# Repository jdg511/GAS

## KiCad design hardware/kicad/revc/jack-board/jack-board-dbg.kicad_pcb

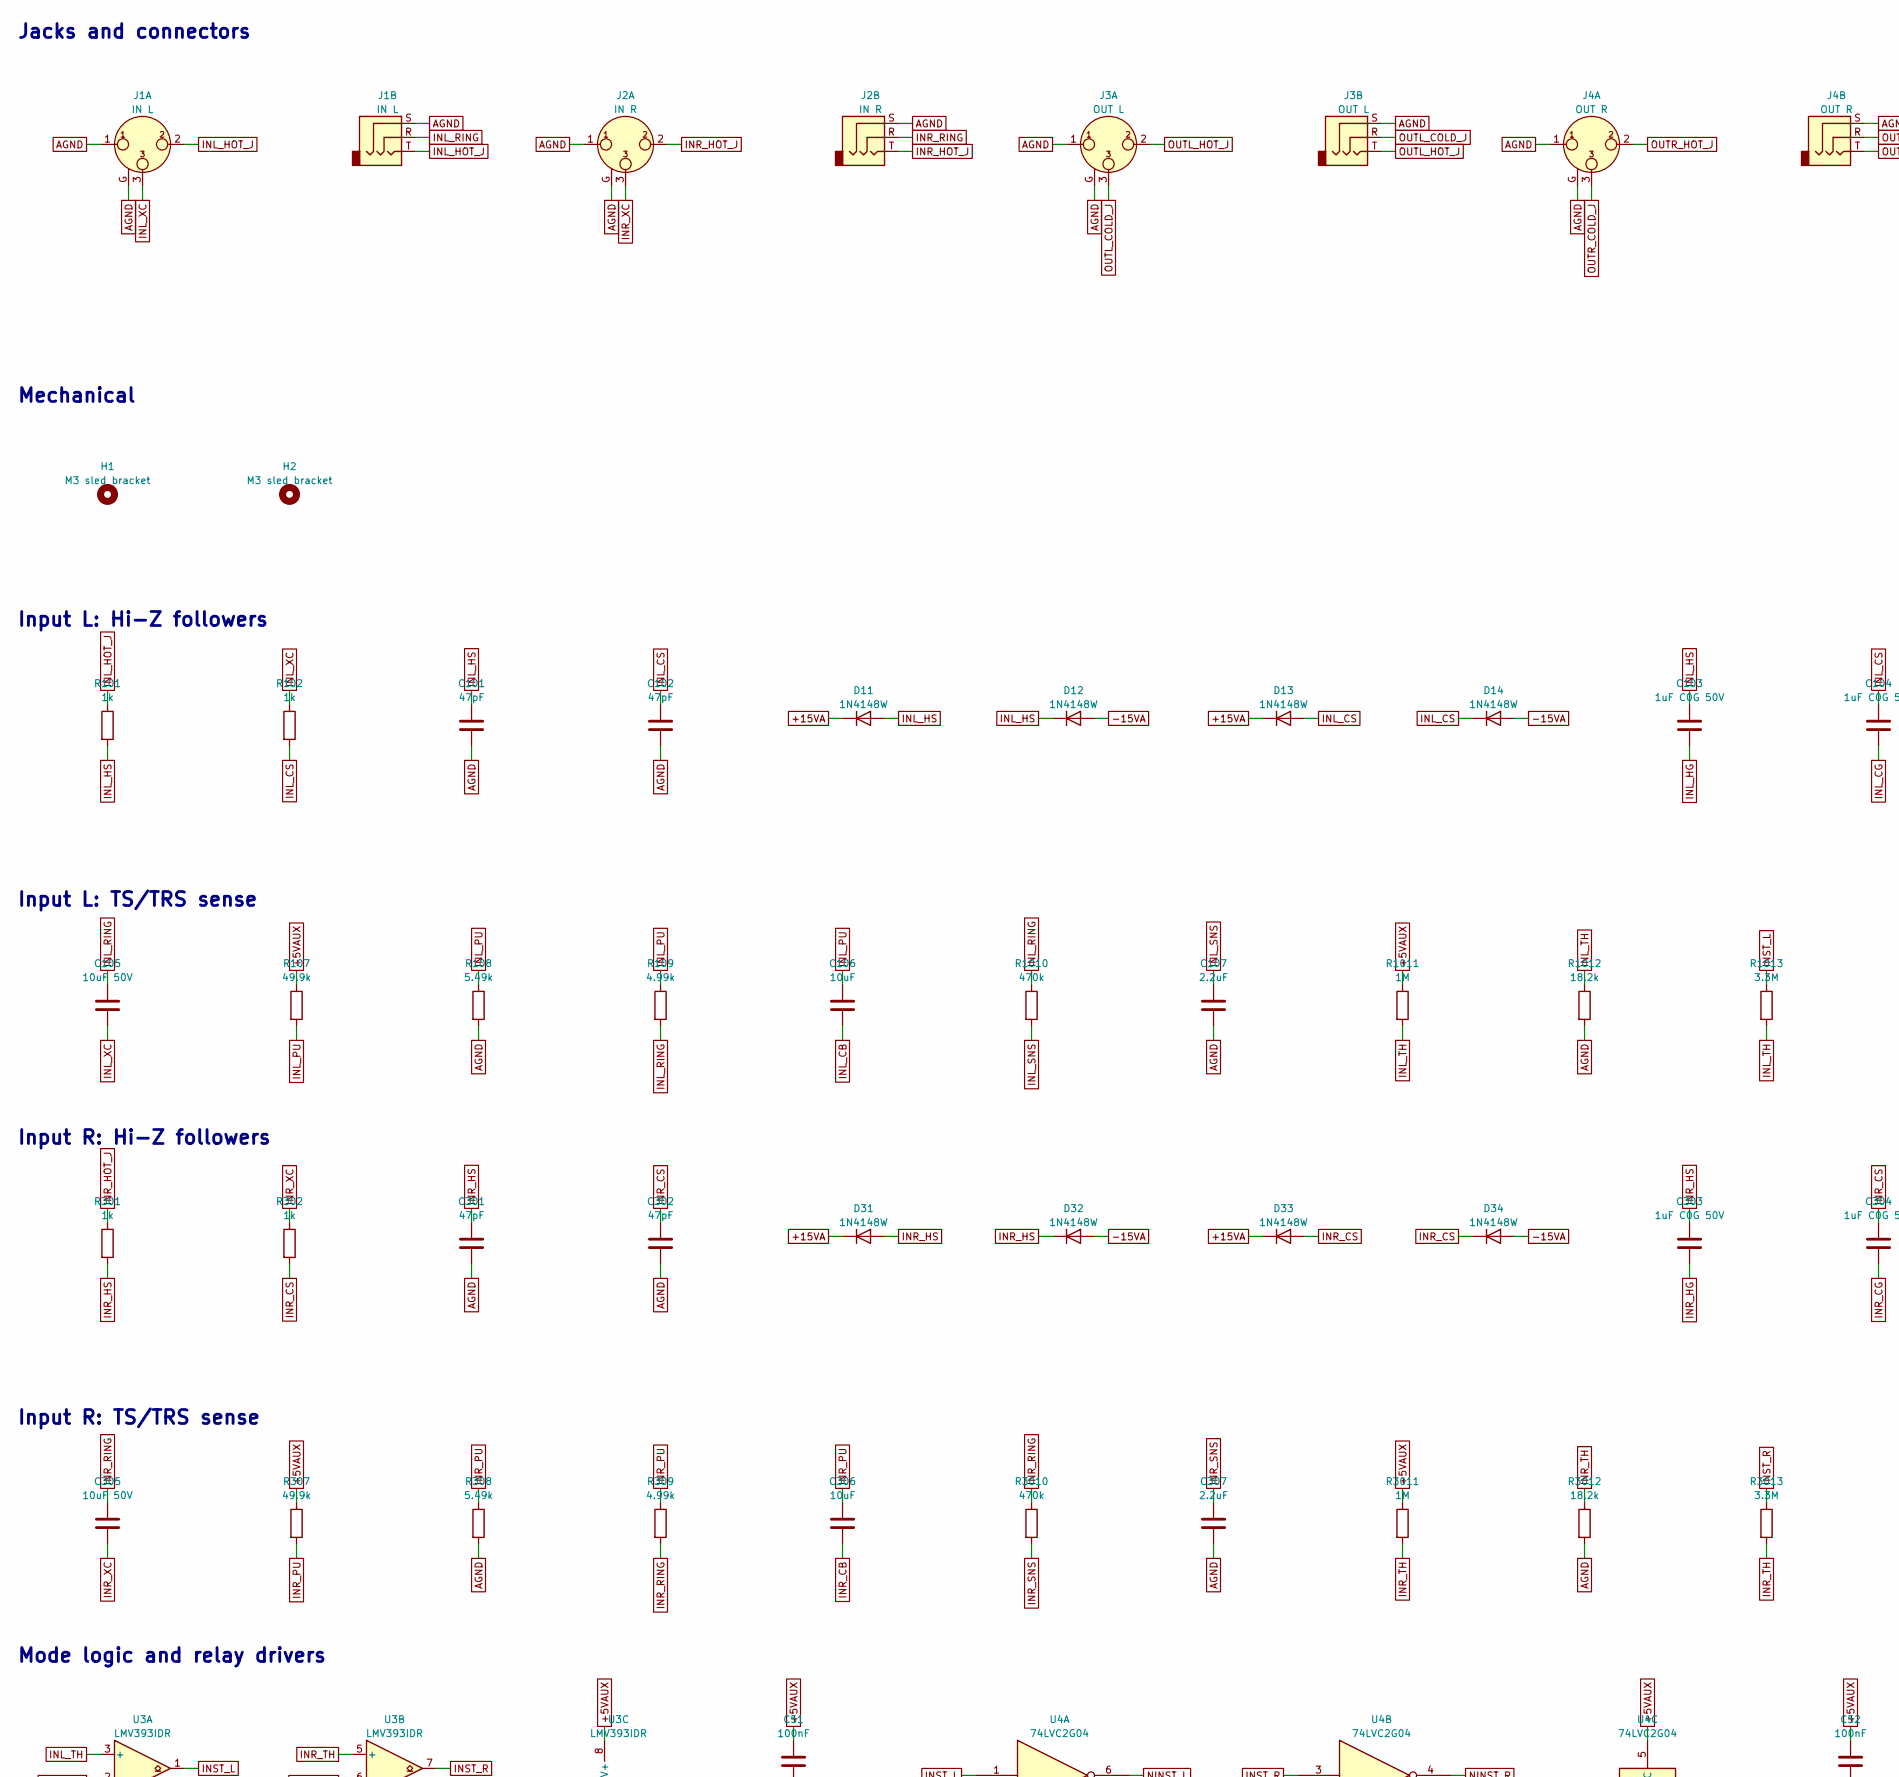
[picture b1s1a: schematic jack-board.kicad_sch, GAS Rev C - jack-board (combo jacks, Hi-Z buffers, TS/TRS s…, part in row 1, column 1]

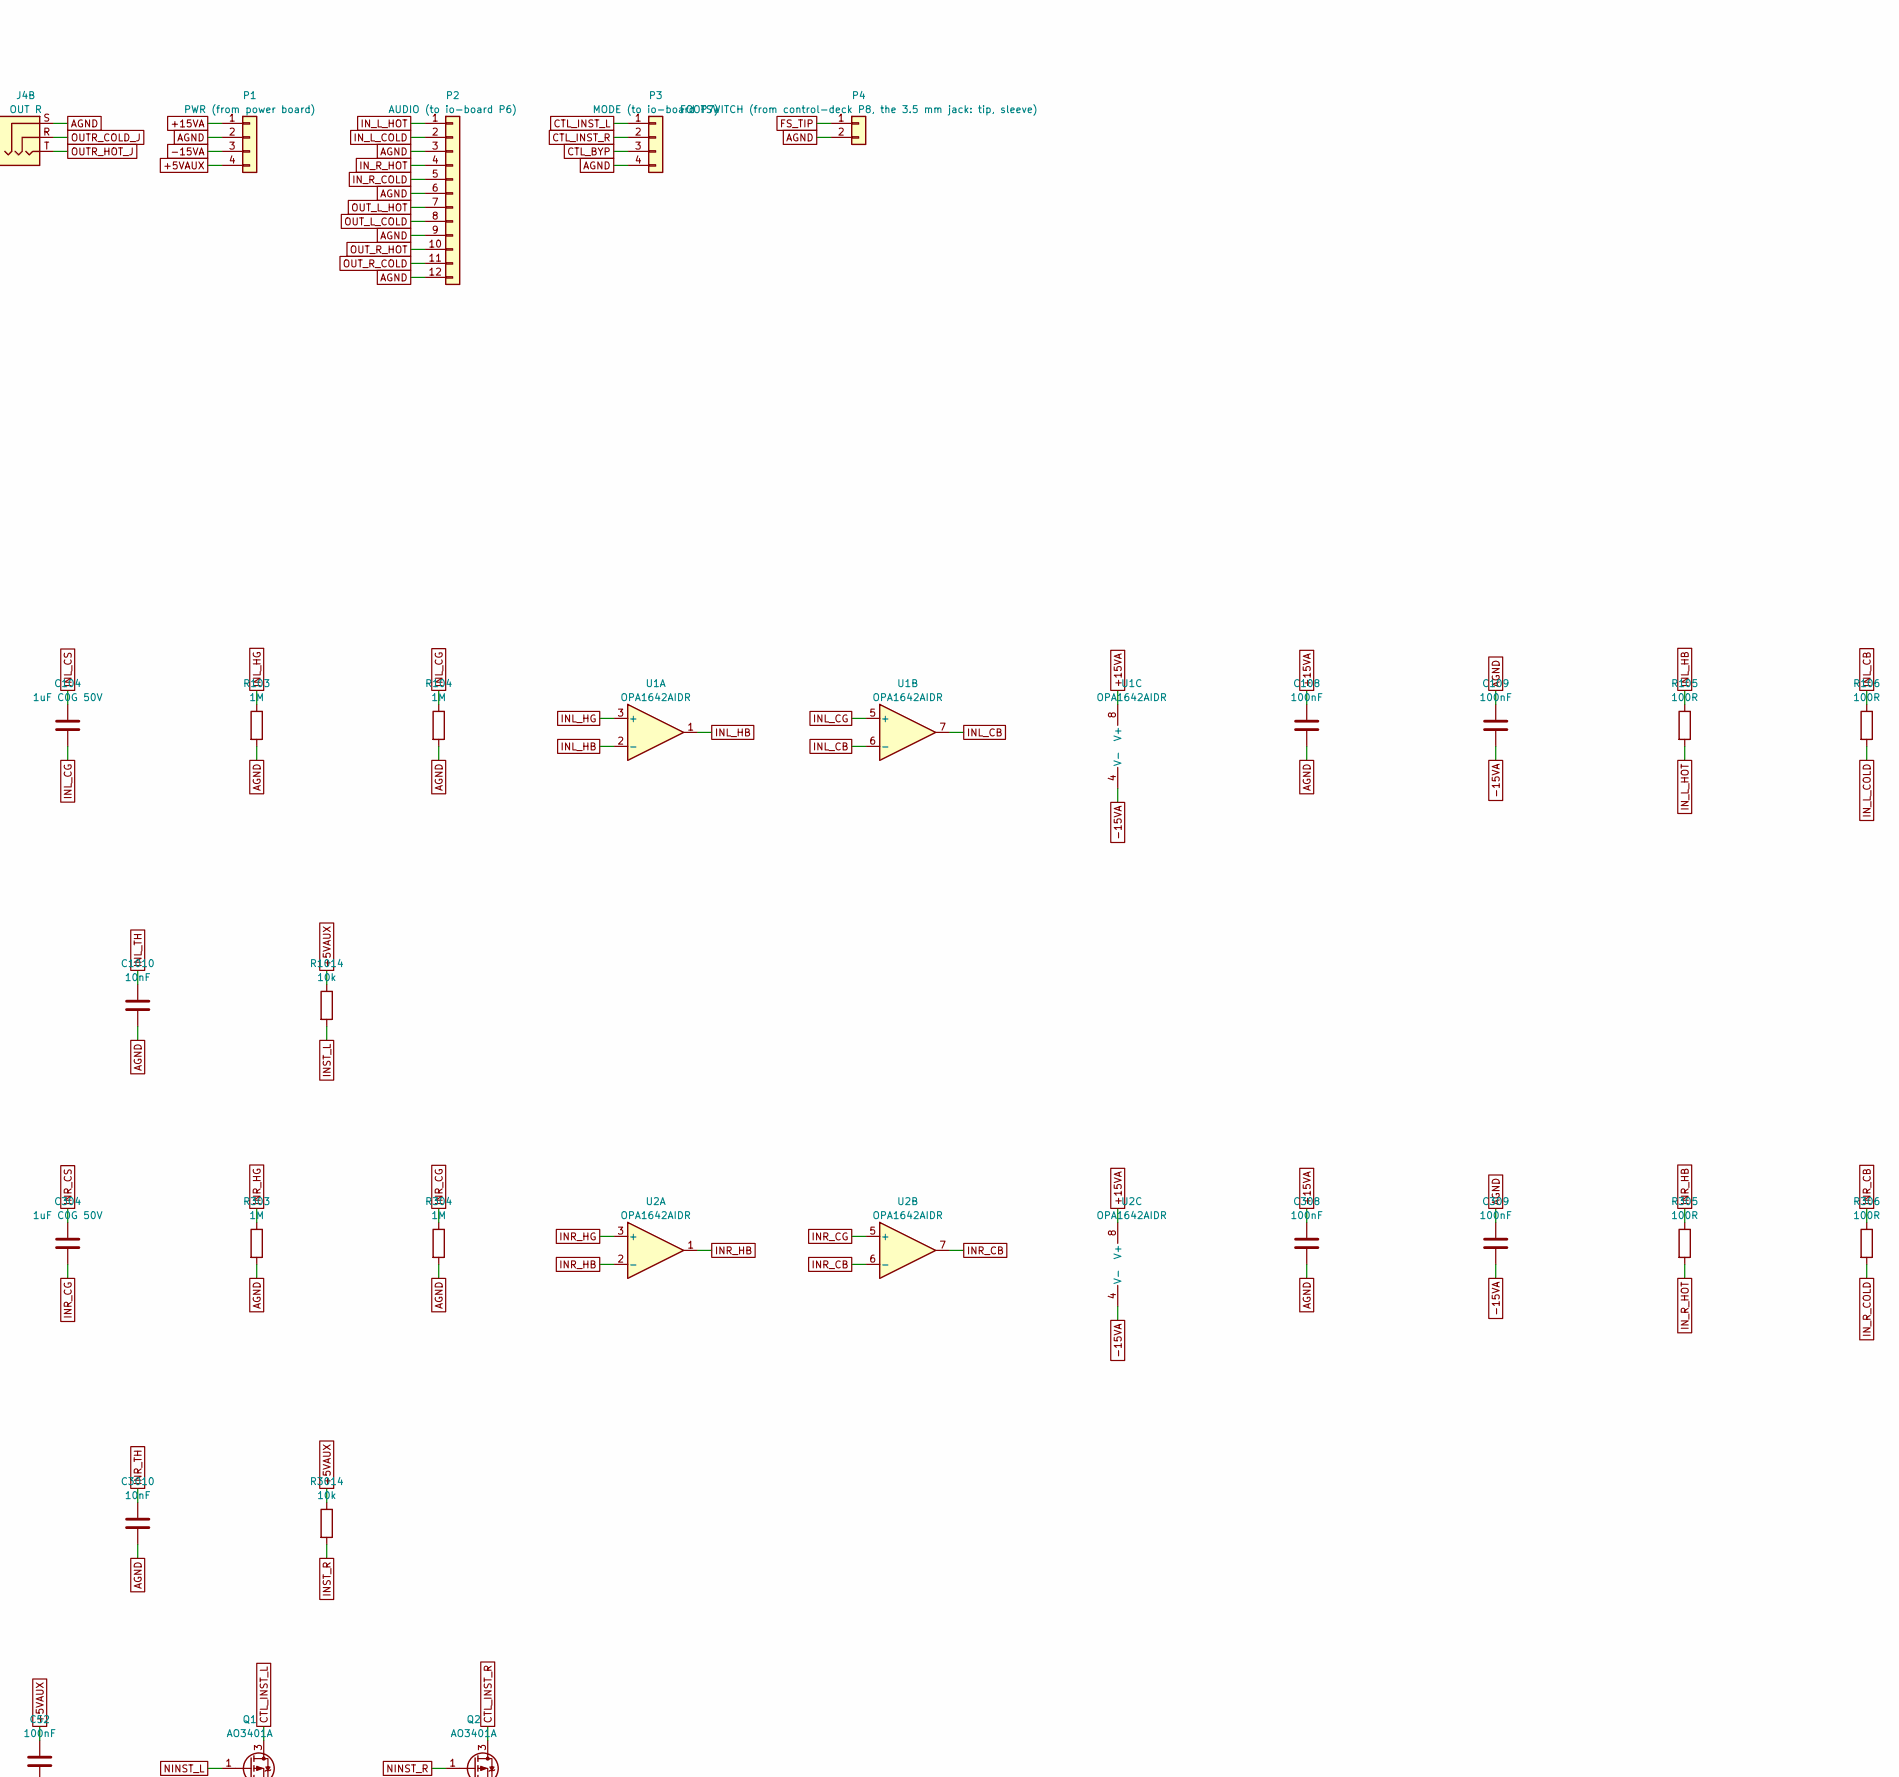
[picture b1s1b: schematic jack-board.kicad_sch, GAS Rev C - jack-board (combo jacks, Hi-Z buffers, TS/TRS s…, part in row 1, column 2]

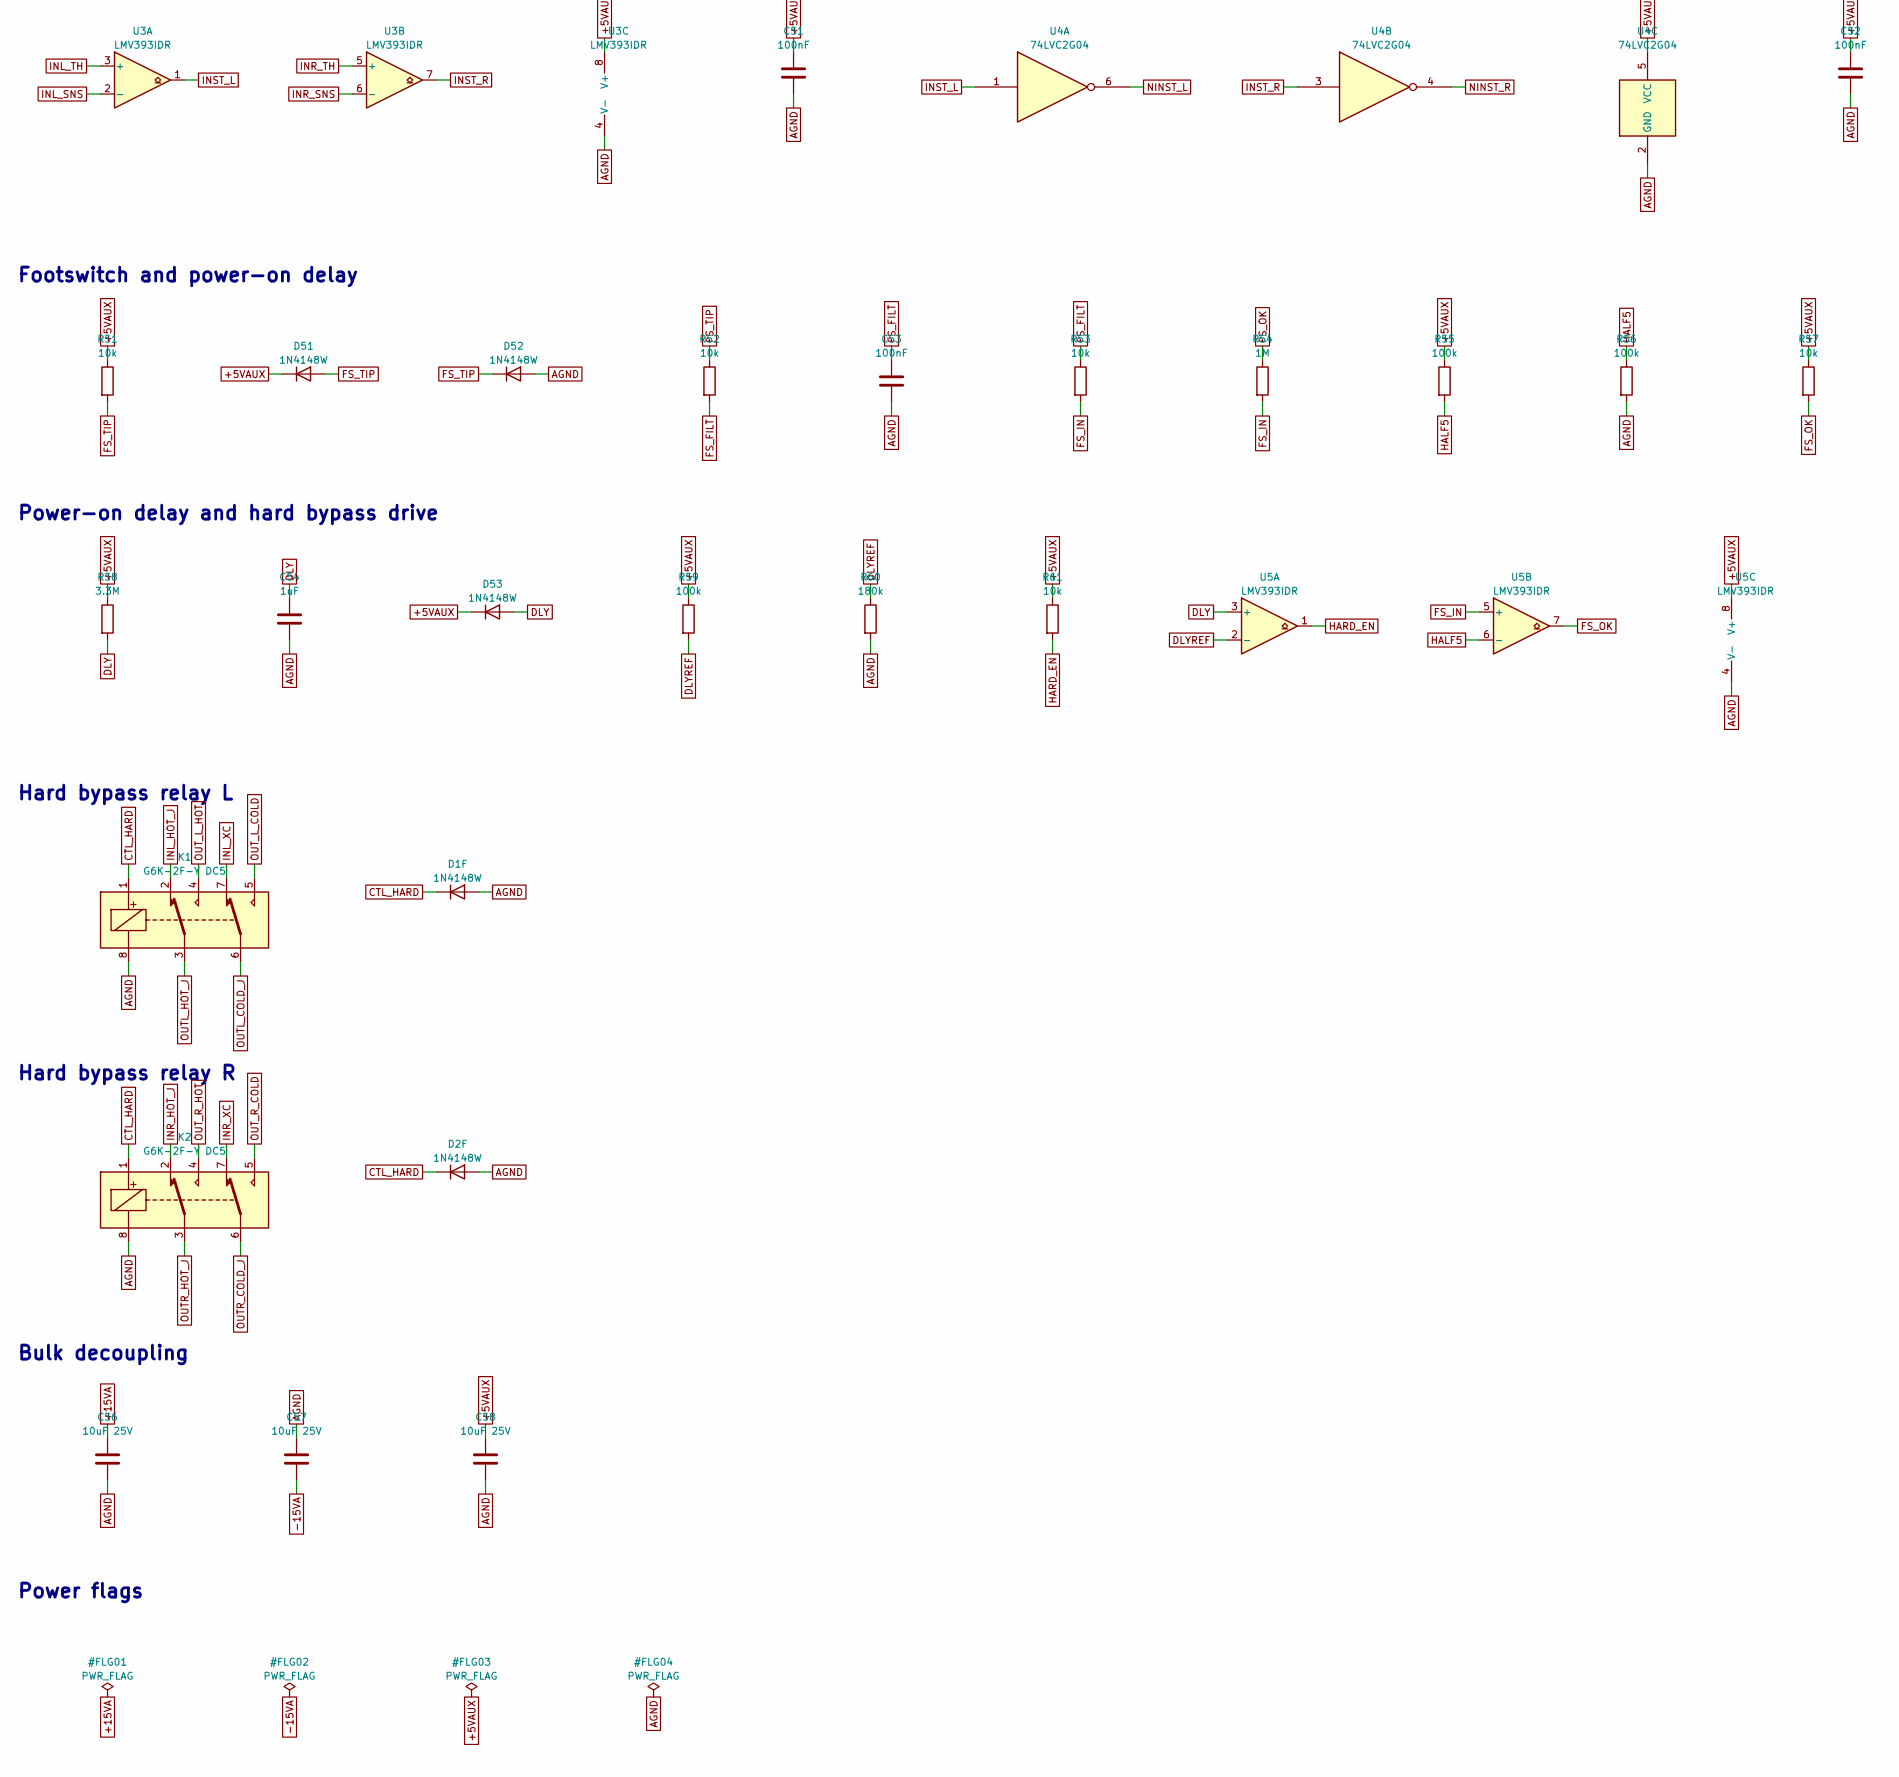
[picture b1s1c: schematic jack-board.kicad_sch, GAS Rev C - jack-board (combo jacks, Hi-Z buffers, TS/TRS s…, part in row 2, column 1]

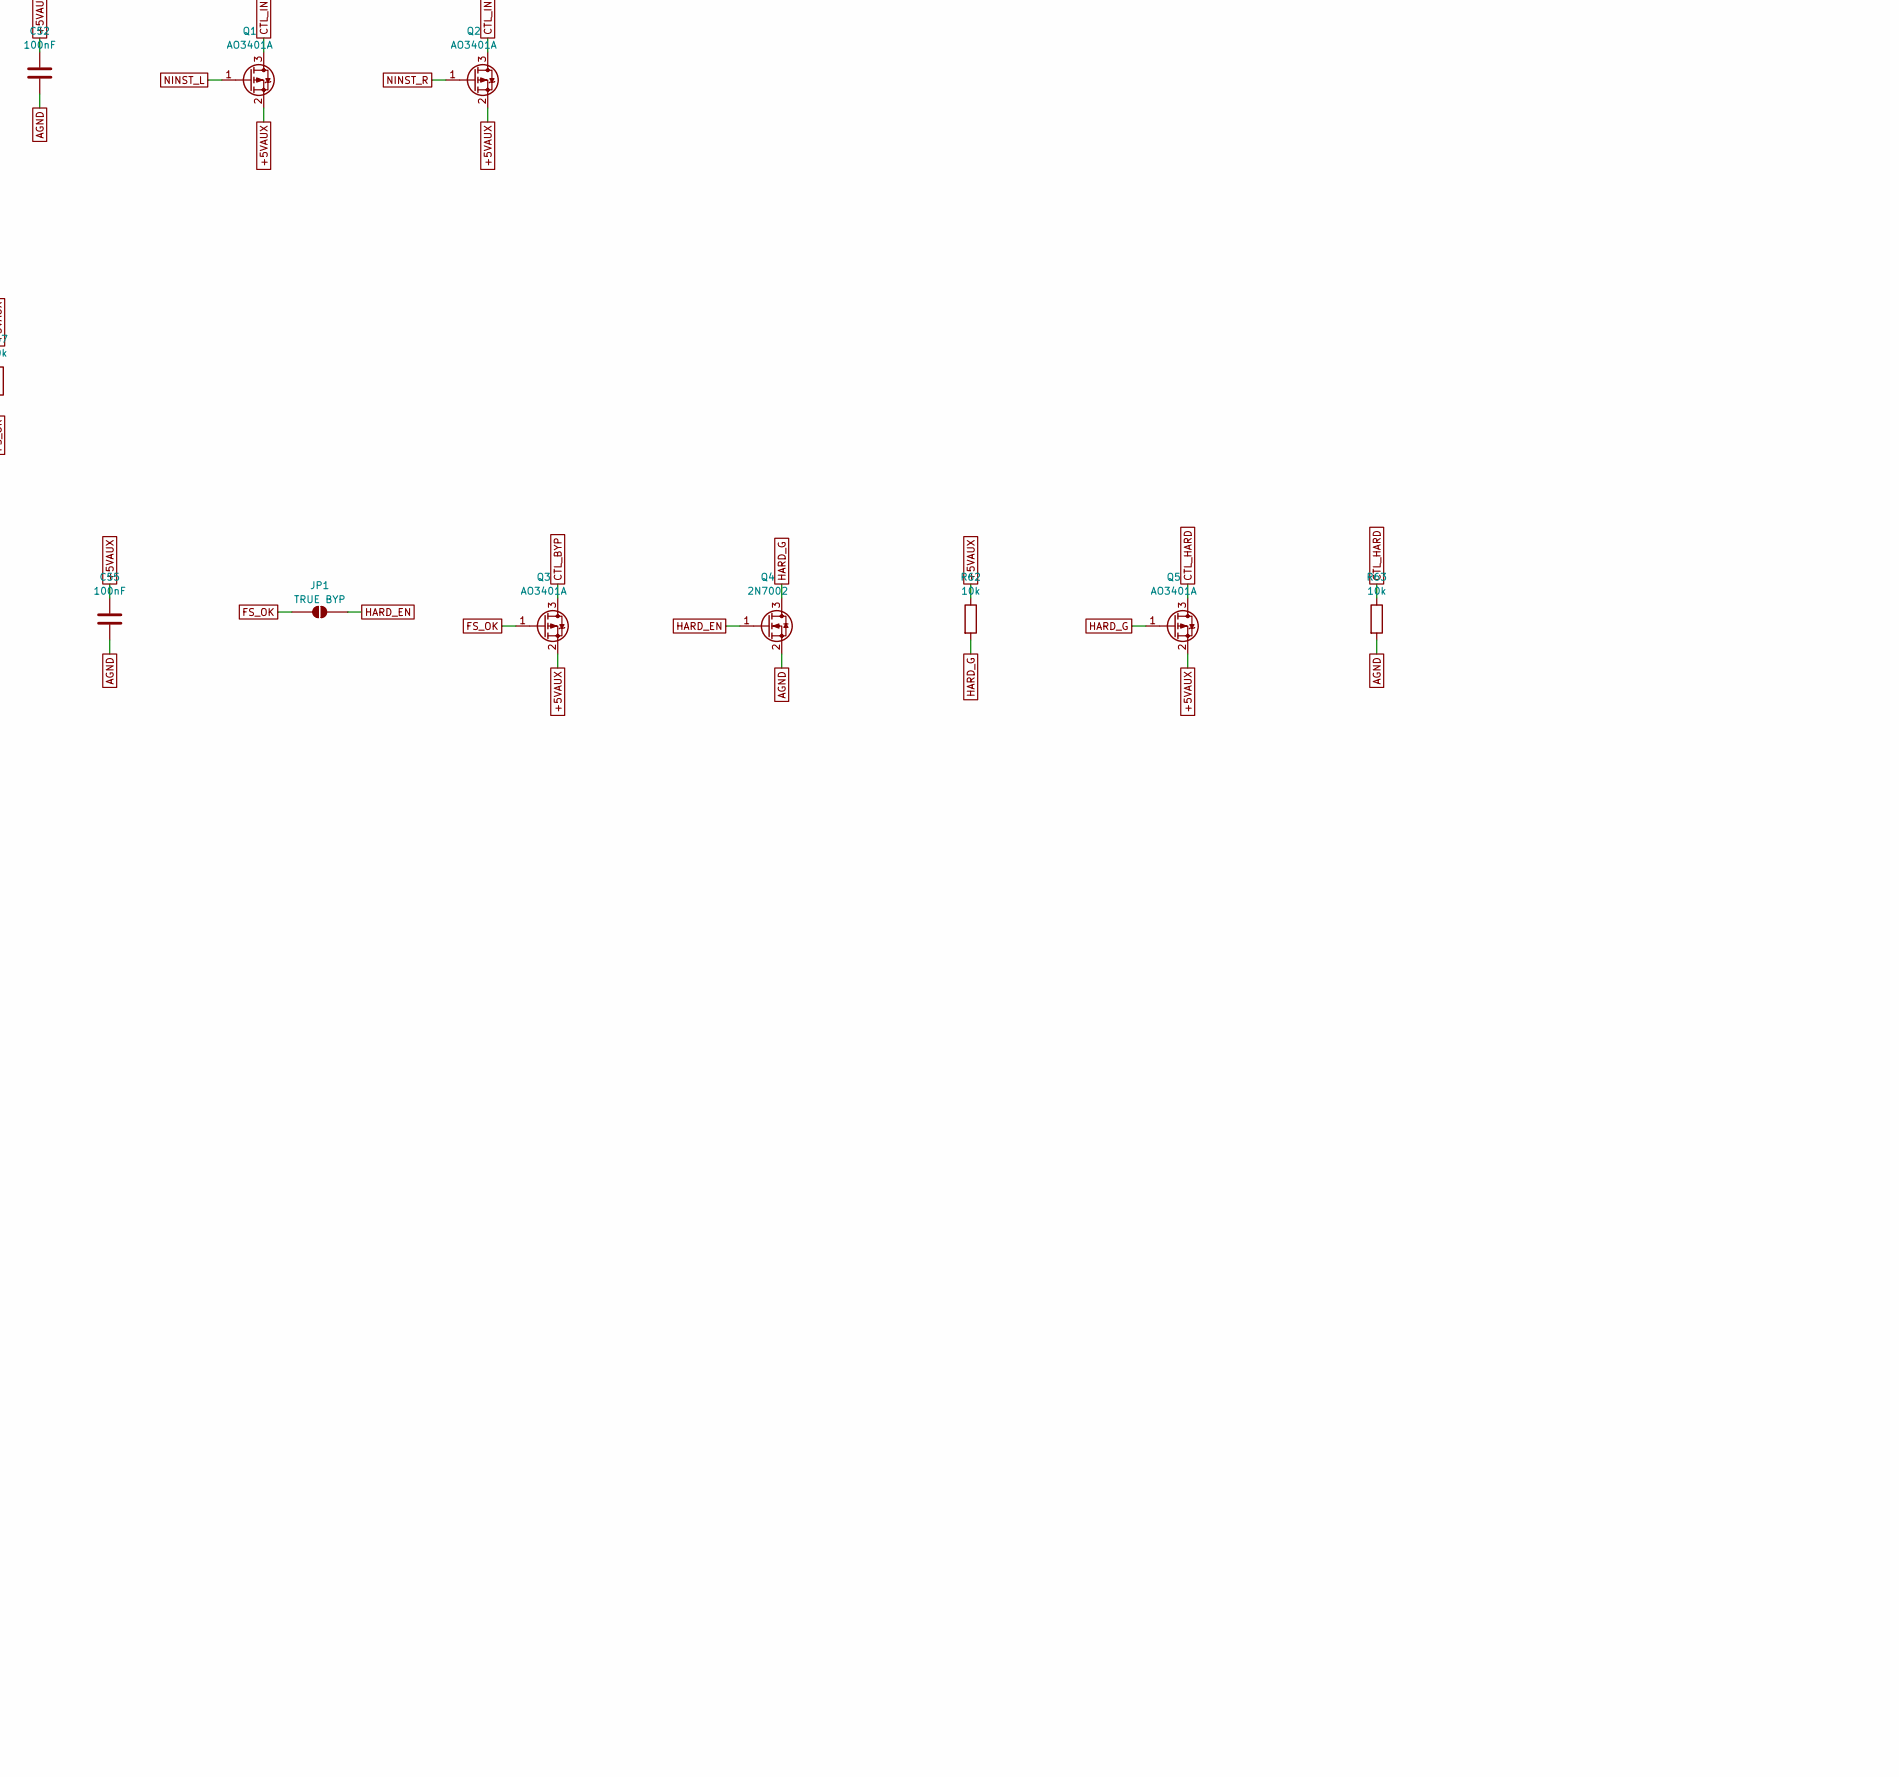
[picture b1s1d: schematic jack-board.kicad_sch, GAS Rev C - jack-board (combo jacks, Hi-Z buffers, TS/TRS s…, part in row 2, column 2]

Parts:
C51, C52, C53, C55, C108, C109, C308, C309: 100nF; C_0603_1608Metric; MPN CL10B104KB8NNNC
C54: 1uF; C_0805_2012Metric; MPN CL21B105KBFNNNE
C56, C57, C58: 10uF 25V; C_0805_2012Metric; MPN CL21A106KAYNNNE
C101, C102, C301, C302: 47pF; C_0603_1608Metric; MPN CL10C470JB8NNNC
C103, C104, C303, C304: 1uF C0G 50V; C_1210_3225Metric; MPN C3225C0G1H105J250AA
C105, C305: 10uF 50V; C_1206_3216Metric; MPN CL31A106KBHNNNE
C106, C306: 10uF; C_0805_2012Metric; MPN CL21A106KAYNNNE
C107, C307: 2.2uF; C_0805_2012Metric; MPN CL21A225KAFNNNE
C1010, C3010: 10nF; C_0603_1608Metric; MPN CL10B103KB8NNNC
D1F, D2F, D11, D12, D13, D14, D31, D32, D33, D34, D51, D52, D53: 1N4148W; D_SOD-123; MPN 1N4148W-7-F
H1, H2: M3 sled bracket; MountingHole_3.2mm_M3
J1: IN L; Jack_XLR-6.35mm_Neutrik_NCJ6FI-V_Vertical; MPN NCJ6FI-V
J2: IN R; Jack_XLR-6.35mm_Neutrik_NCJ6FI-V_Vertical; MPN NCJ6FI-V
J3: OUT L; Jack_XLR-6.35mm_Neutrik_NCJ6FI-V_Vertical; MPN NCJ6FI-V
J4: OUT R; Jack_XLR-6.35mm_Neutrik_NCJ6FI-V_Vertical; MPN NCJ6FI-V
JP1: TRUE BYP; SolderJumper-2_P1.3mm_Open_RoundedPad1.0x1.5mm
K1, K2: G6K-2F-Y DC5; Relay_DPDT_Omron_G6K-2F-Y; MPN G6K-2F-Y DC5
P1: PWR (from power board); JST_VH_B4P-VH_1x04_P3.96mm_Vertical; MPN B4P-VH(LF)(SN)
P2: AUDIO (to io-board P6); JST_XH_B12B-XH-A_1x12_P2.50mm_Vertical; MPN B12B-XH-A(LF)(SN)
P3: MODE (to io-board P7); JST_XH_B4B-XH-A_1x04_P2.50mm_Vertical; MPN B4B-XH-A(LF)(SN)
P4: FOOTSWITCH (from control-deck P8, the 3.5 mm jack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; JST_XH_B2B-XH-A_1x02_P2.50mm_Vertical; MPN B2B-XH-A(LF)(SN)
Q1, Q2, Q3, Q5: AO3401A; SOT-23; MPN AO3401A
Q4: 2N7002; SOT-23; MPN 2N7002-7-F
R51, R52, R53, R57, R61, R62, R63, R1014, R3014: 10k; R_0603_1608Metric; MPN RC0603FR-0710KL
R54, R103, R104, R303, R304, R1011, R3011: 1M; R_0603_1608Metric; MPN RC0603FR-071ML
R55, R56, R59: 100k; R_0603_1608Metric; MPN RC0603FR-07100KL
R58, R1013, R3013: 3.3M; R_0603_1608Metric; MPN RC0603FR-073M3L
R60: 180k; R_0603_1608Metric; MPN RC0603FR-07180KL
R101, R102, R301, R302: 1k; R_0603_1608Metric; MPN RC0603FR-071KL
R105, R106, R305, R306: 100R; R_0603_1608Metric; MPN RC0603FR-07100RL
R107, R307: 49.9k; R_0603_1608Metric; MPN RC0603FR-0749K9L
R108, R308: 5.49k; R_0603_1608Metric; MPN RC0603FR-075K49L
R109, R309: 4.99k; R_0603_1608Metric; MPN RC0603FR-074K99L
R1010, R3010: 470k; R_0603_1608Metric; MPN RC0603FR-07470KL
R1012, R3012: 18.2k; R_0603_1608Metric; MPN RC0603FR-0718K2L
U1, U2: OPA1642AIDR; SOIC-8_3.9x4.9mm_P1.27mm; MPN OPA1642AIDR
U3, U5: LMV393IDR; SOIC-8_3.9x4.9mm_P1.27mm; MPN LMV393IDR
U4: 74LVC2G04; SOT-23-6; MPN 74LVC2G04GV,125

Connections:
+5VAUX: C51.1, C52.1, C55.1, C58.1, D51.1 (K), D53.1 (K), P1.4, Q1.2 (S), Q2.2 (S), Q3.2 (S), Q5.2 (S), R51.1, R55.1, R57.1, R58.1, R59.1, R61.1, R62.1, R107.1, R307.1, R1011.1, R1014.1, R3011.1, R3014.1, U3.8 (V+), U4.5 (VCC), U5.8 (V+)
+15VA: C56.1, C108.1, C308.1, D11.1 (K), D13.1 (K), D31.1 (K), D33.1 (K), P1.1, U1.8 (V+), U2.8 (V+)
-15VA: C57.2, C109.2, C309.2, D12.2 (A), D14.2 (A), D32.2 (A), D34.2 (A), P1.3, U1.4 (V-), U2.4 (V-)
AGND: C51.2, C52.2, C53.2, C54.2, C55.2, C56.2, C57.1, C58.2, C101.2, C102.2, C107.2, C108.2, C109.1, C301.2, C302.2, C307.2, C308.2, C309.1, C1010.2, C3010.2, D1F.2 (A), D2F.2 (A), D52.2 (A), J1.1, J1.G, J1.S, J2.1, J2.G, J2.S, J3.1, J3.G, J3.S, J4.1, J4.G, J4.S, K1.8, K2.8, P1.2, P2.3, P2.6, P2.9, P2.12, P3.4, P4.2, Q4.2 (S), R56.2, R60.2, R63.2, R103.2, R104.2, R108.2, R303.2, R304.2, R308.2, R1012.2, R3012.2, U3.4 (V-), U4.2 (GND), U5.4 (V-)
CTL_BYP: P3.3, Q3.3 (D)
CTL_HARD: D1F.1 (K), D2F.1 (K), K1.1, K2.1, Q5.3 (D), R63.1
CTL_INST_L: P3.1, Q1.3 (D)
CTL_INST_R: P3.2, Q2.3 (D)
DLY: C54.1, D53.2 (A), R58.2, U5.3 (+)
DLYREF: R59.2, R60.1, U5.2 (-)
FS_FILT: C53.1, R52.2, R53.1
FS_IN: R53.2, R54.2, U5.5 (+)
FS_OK: JP1.1 (A), Q3.1 (G), R54.1, R57.2, U5.7
FS_TIP: D51.2 (A), D52.1 (K), P4.1, R51.2, R52.1
HALF5: R55.2, R56.1, U5.6 (-)
HARD_EN: JP1.2 (B), Q4.1 (G), R61.2, U5.1
HARD_G: Q4.3 (D), Q5.1 (G), R62.2
INL_CB: C106.2, R106.1, U1.6 (-), U1.7
INL_CG: C104.2, R104.1, U1.5 (+)
INL_CS: C102.1, C104.1, D13.2 (A), D14.1 (K), R102.2
INL_HB: R105.1, U1.1, U1.2 (-)
INL_HG: C103.2, R103.1, U1.3 (+)
INL_HOT_J: J1.2, J1.T, K1.2, R101.1
INL_HS: C101.1, C103.1, D11.2 (A), D12.1 (K), R101.2
INL_PU: C106.1, R107.2, R108.1, R109.1
INL_RING: C105.1, J1.R, R109.2, R1010.1
INL_SNS: C107.1, R1010.2, U3.2 (-)
INL_TH: C1010.1, R1011.2, R1012.1, R1013.2, U3.3 (+)
INL_XC: C105.2, J1.3, K1.7, R102.1
INR_CB: C306.2, R306.1, U2.6 (-), U2.7
INR_CG: C304.2, R304.1, U2.5 (+)
INR_CS: C302.1, C304.1, D33.2 (A), D34.1 (K), R302.2
INR_HB: R305.1, U2.1, U2.2 (-)
INR_HG: C303.2, R303.1, U2.3 (+)
INR_HOT_J: J2.2, J2.T, K2.2, R301.1
INR_HS: C301.1, C303.1, D31.2 (A), D32.1 (K), R301.2
INR_PU: C306.1, R307.2, R308.1, R309.1
INR_RING: C305.1, J2.R, R309.2, R3010.1
INR_SNS: C307.1, R3010.2, U3.6 (-)
INR_TH: C3010.1, R3011.2, R3012.1, R3013.2, U3.5 (+)
INR_XC: C305.2, J2.3, K2.7, R302.1
INST_L: R1013.1, R1014.2, U3.1, U4.1
INST_R: R3013.1, R3014.2, U3.7, U4.3
IN_L_COLD: P2.2, R106.2
IN_L_HOT: P2.1, R105.2
IN_R_COLD: P2.5, R306.2
IN_R_HOT: P2.4, R305.2
NINST_L: Q1.1 (G), U4.6
NINST_R: Q2.1 (G), U4.4
OUTL_COLD_J: J3.3, J3.R, K1.6
OUTL_HOT_J: J3.2, J3.T, K1.3
OUTR_COLD_J: J4.3, J4.R, K2.6
OUTR_HOT_J: J4.2, J4.T, K2.3
OUT_L_COLD: K1.5, P2.8
OUT_L_HOT: K1.4, P2.7
OUT_R_COLD: K2.5, P2.11
OUT_R_HOT: K2.4, P2.10

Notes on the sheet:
Jacks and connectors
Mechanical
Input L: Hi-Z followers
Input L: TS/TRS sense
Input R: Hi-Z followers
Input R: TS/TRS sense
Mode logic and relay drivers
Footswitch and power-on delay
Power-on delay and hard bypass drive
Hard bypass relay L
Hard bypass relay R
Bulk decoupling
Power flags

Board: 2 copper layers, 105 parts (4 on the bottom side), 57 nets, no tracks yet.

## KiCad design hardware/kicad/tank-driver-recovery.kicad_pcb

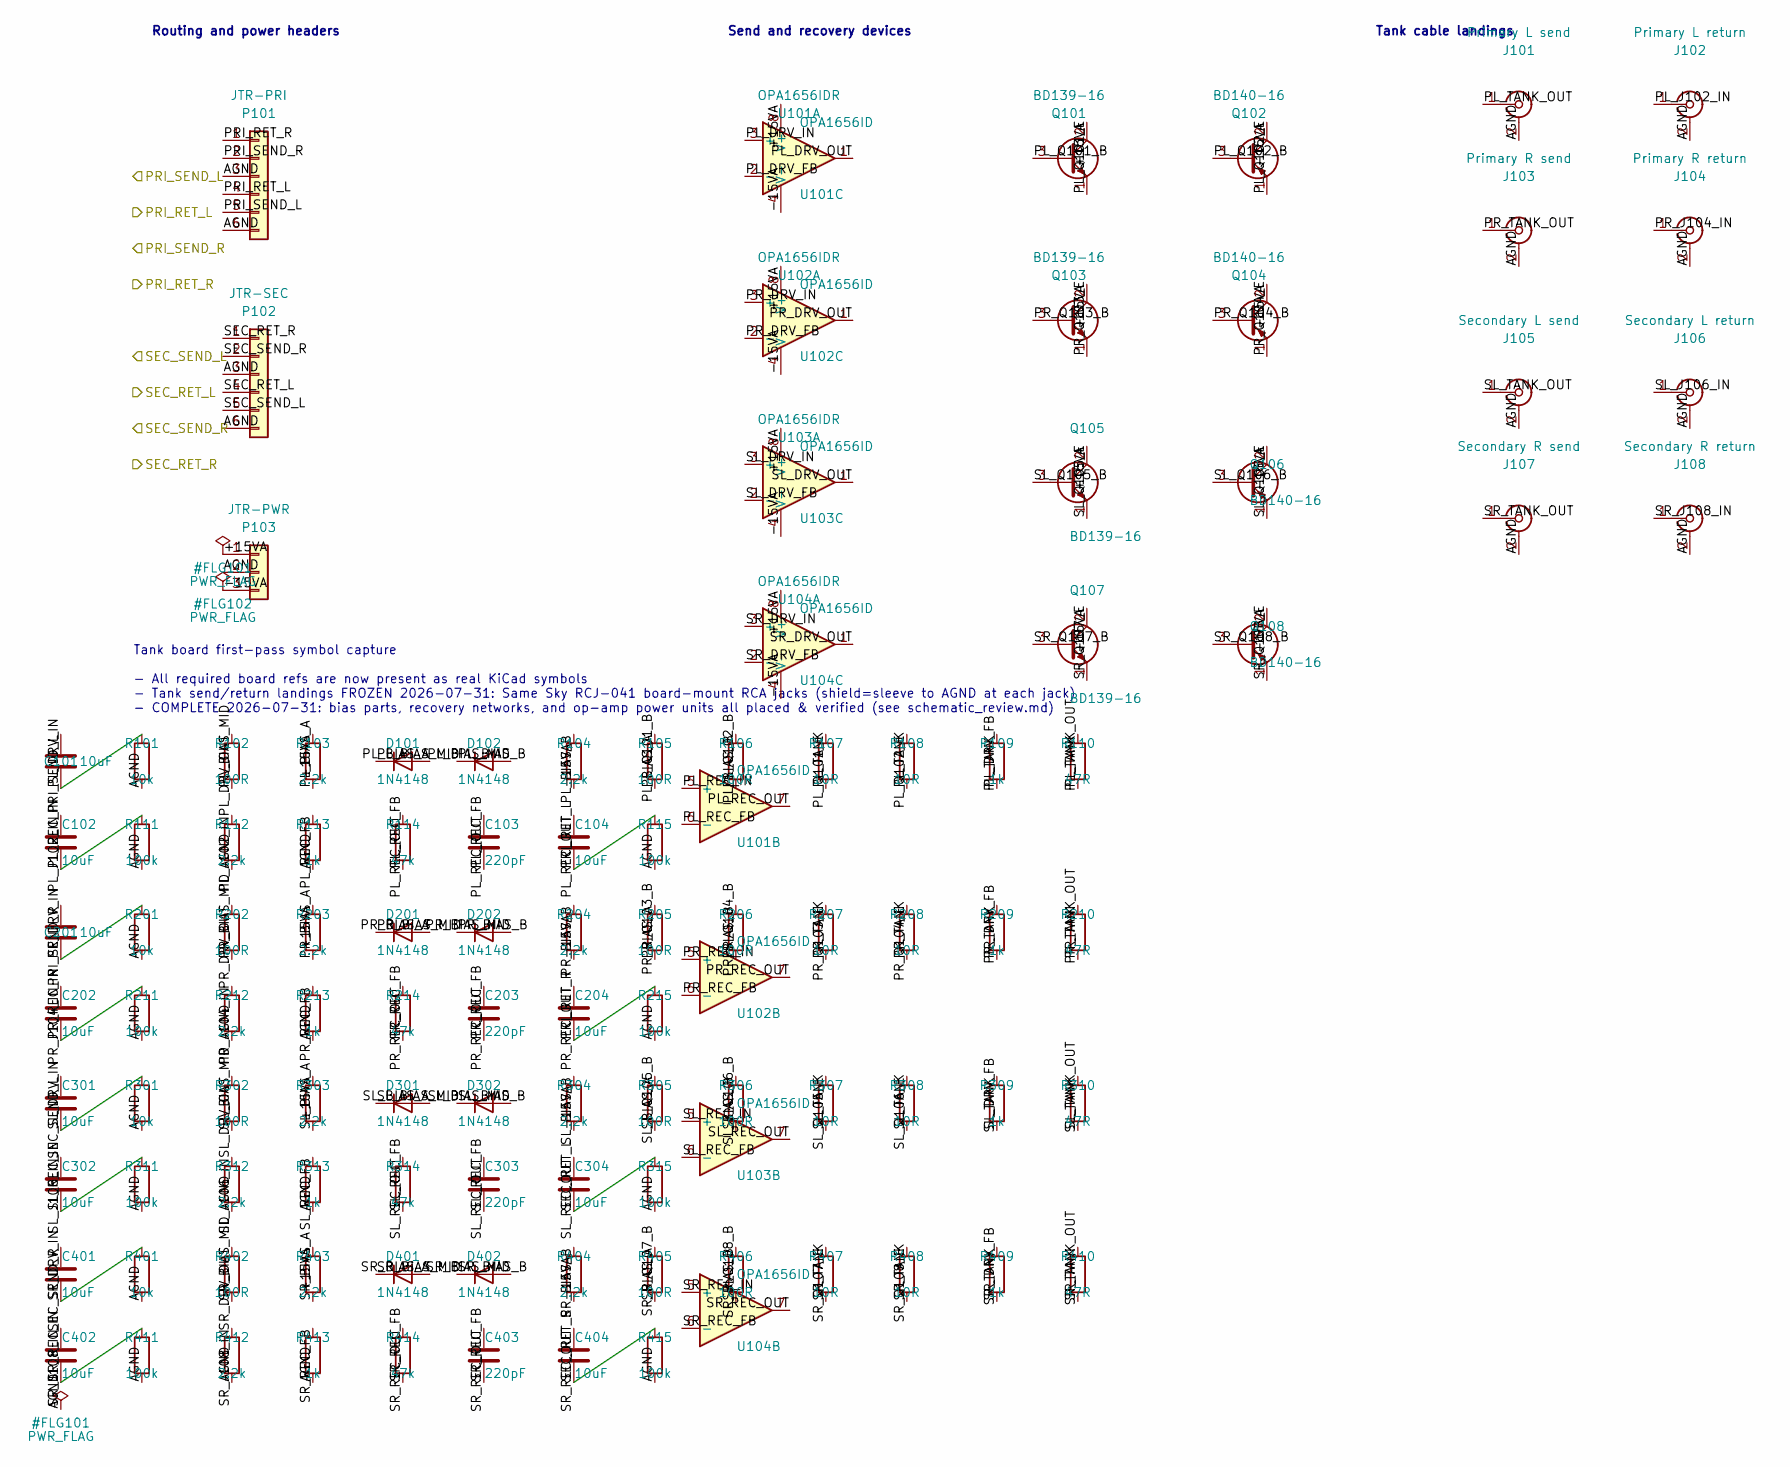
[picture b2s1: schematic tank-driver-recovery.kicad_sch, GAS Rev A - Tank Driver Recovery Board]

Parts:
C101, C102, C104, C201, C202, C204, C301, C302, C304, C401, C402, C404: 10uF; CP_Elec_5x5.8
C103, C203, C303, C403: 220pF; C_0603_1608Metric
D101, D102, D201, D202, D301, D302, D401, D402: 1N4148; D_SOD-123
J101: Primary L send; Jack_RCA_SameSky_RCJ-041_Horizontal; MPN RCJ-041
J102: Primary L return; Jack_RCA_SameSky_RCJ-041_Horizontal; MPN RCJ-041
J103: Primary R send; Jack_RCA_SameSky_RCJ-041_Horizontal; MPN RCJ-041
J104: Primary R return; Jack_RCA_SameSky_RCJ-041_Horizontal; MPN RCJ-041
J105: Secondary L send; Jack_RCA_SameSky_RCJ-041_Horizontal; MPN RCJ-041
J106: Secondary L return; Jack_RCA_SameSky_RCJ-041_Horizontal; MPN RCJ-041
J107: Secondary R send; Jack_RCA_SameSky_RCJ-041_Horizontal; MPN RCJ-041
J108: Secondary R return; Jack_RCA_SameSky_RCJ-041_Horizontal; MPN RCJ-041
P101: JTR-PRI; JST_XH_B6B-XH-A_1x06_P2.50mm_Vertical
P102: JTR-SEC; JST_XH_B6B-XH-A_1x06_P2.50mm_Vertical
P103: JTR-PWR; JST_VH_B3P-VH_1x03_P3.96mm_Vertical
Q101, Q103, Q105, Q107: BD139-16; TO-126-3_Vertical
Q102, Q104, Q106, Q108: BD140-16; TO-126-3_Vertical
R101, R201, R301, R401: 10k; R_0603_1608Metric
R102, R105, R106, R202, R205, R206, R302, R305, R306, R402, R405, R406: 100R; R_0603_1608Metric
R103, R104, R112, R203, R204, R212, R303, R304, R312, R403, R404, R412: 2.2k; R_0603_1608Metric
R107, R108, R207, R208, R307, R308, R407, R408: 10R; R_1206_3216Metric
R109, R113, R209, R213, R309, R313, R409, R413: 1k; R_0603_1608Metric
R110, R210, R310, R410: 47R; R_0603_1608Metric
R111, R115, R211, R215, R311, R315, R411, R415: 100k; R_0603_1608Metric
R114, R214, R314, R414: 47k; R_0603_1608Metric
U101, U102, U103, U104: OPA1656IDR; SOIC-8_3.9x4.9mm_P1.27mm

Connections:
+15VA: P103.1, Q101.2 (C), Q103.2 (C), Q105.2 (C), Q107.2 (C), R103.1, R203.1, R303.1, R403.1, U101.8 (V+), U102.8 (V+), U103.8 (V+), U104.8 (V+)
AGND: J101.2 (Ext), J102.2 (Ext), J103.2 (Ext), J104.2 (Ext), J105.2 (Ext), J106.2 (Ext), J107.2 (Ext), J108.2 (Ext), P101.3, P101.6, P102.3, P102.6, P103.2, R101.2, R111.2, R112.2, R113.2, R115.2, R201.2, R211.2, R212.2, R213.2, R215.2, R301.2, R311.2, R312.2, R313.2, R315.2, R401.2, R411.2, R412.2, R413.2, R415.2
PL_BIAS_A: D101.2 (A), R103.2, R105.1
PL_BIAS_B: D102.1 (K), R104.1, R106.1
PL_BIAS_MID: D101.1 (K), D102.2 (A), R102.2
PL_DRV_FB: R109.2, U101.2 (-)
PL_DRV_IN: C101.2, R101.1, U101.3 (+)
PL_DRV_OUT: R102.1, U101.1
PL_J102_IN: C102.1, J102.1 (In), R112.1
PL_Q101_B: Q101.3 (B), R105.2
PL_Q101_E: Q101.1 (E), R107.1
PL_Q102_B: Q102.3 (B), R106.2
PL_Q102_E: Q102.1 (E), R108.1
PL_REC_FB: C103.2, R113.1, R114.2, U101.6 (-)
PL_REC_IN: C102.2, R111.1, U101.5 (+)
PL_REC_OUT: C103.1, C104.1, R114.1, U101.7
PL_TANK: R107.2, R108.2, R109.1, R110.1
PL_TANK_OUT: J101.1 (In), R110.2
PRI_RET_L: C104.2, P101.4, R115.1
PRI_RET_R: C204.2, P101.1, R215.1
PRI_SEND_L: C101.1, P101.5
PRI_SEND_R: C201.1, P101.2
PR_BIAS_A: D201.2 (A), R203.2, R205.1
PR_BIAS_B: D202.1 (K), R204.1, R206.1
PR_BIAS_MID: D201.1 (K), D202.2 (A), R202.2
PR_DRV_FB: R209.2, U102.2 (-)
PR_DRV_IN: C201.2, R201.1, U102.3 (+)
PR_DRV_OUT: R202.1, U102.1
PR_J104_IN: C202.1, J104.1 (In), R212.1
PR_Q103_B: Q103.3 (B), R205.2
PR_Q103_E: Q103.1 (E), R207.1
PR_Q104_B: Q104.3 (B), R206.2
PR_Q104_E: Q104.1 (E), R208.1
PR_REC_FB: C203.2, R213.1, R214.2, U102.6 (-)
PR_REC_IN: C202.2, R211.1, U102.5 (+)
PR_REC_OUT: C203.1, C204.1, R214.1, U102.7
PR_TANK: R207.2, R208.2, R209.1, R210.1
PR_TANK_OUT: J103.1 (In), R210.2
SEC_RET_L: C304.2, P102.4, R315.1
SEC_RET_R: C404.2, P102.1, R415.1
SEC_SEND_L: C301.1, P102.5
SEC_SEND_R: C401.1, P102.2
SL_BIAS_A: D301.2 (A), R303.2, R305.1
SL_BIAS_B: D302.1 (K), R304.1, R306.1
SL_BIAS_MID: D301.1 (K), D302.2 (A), R302.2
SL_DRV_FB: R309.2, U103.2 (-)
SL_DRV_IN: C301.2, R301.1, U103.3 (+)
SL_DRV_OUT: R302.1, U103.1
SL_J106_IN: C302.1, J106.1 (In), R312.1
SL_Q105_B: Q105.3 (B), R305.2
SL_Q105_E: Q105.1 (E), R307.1
SL_Q106_B: Q106.3 (B), R306.2
SL_Q106_E: Q106.1 (E), R308.1
SL_REC_FB: C303.2, R313.1, R314.2, U103.6 (-)
SL_REC_IN: C302.2, R311.1, U103.5 (+)
SL_REC_OUT: C303.1, C304.1, R314.1, U103.7
SL_TANK: R307.2, R308.2, R309.1, R310.1
SL_TANK_OUT: J105.1 (In), R310.2
SR_BIAS_A: D401.2 (A), R403.2, R405.1
SR_BIAS_B: D402.1 (K), R404.1, R406.1
SR_BIAS_MID: D401.1 (K), D402.2 (A), R402.2
SR_DRV_FB: R409.2, U104.2 (-)
SR_DRV_IN: C401.2, R401.1, U104.3 (+)
SR_DRV_OUT: R402.1, U104.1
SR_J108_IN: C402.1, J108.1 (In), R412.1
SR_Q107_B: Q107.3 (B), R405.2
SR_Q107_E: Q107.1 (E), R407.1
SR_Q108_B: Q108.3 (B), R406.2
SR_Q108_E: Q108.1 (E), R408.1
SR_REC_FB: C403.2, R413.1, R414.2, U104.6 (-)
SR_REC_IN: C402.2, R411.1, U104.5 (+)
SR_REC_OUT: C403.1, C404.1, R414.1, U104.7
SR_TANK: R407.2, R408.2, R409.1, R410.1
SR_TANK_OUT: J107.1 (In), R410.2

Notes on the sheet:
Tank board first-pass symbol capture - All required board refs are now present as real KiCad symbols - Tank send/return landings FROZEN 2026-07-31: Same Sky RCJ-041 board-mount RCA jacks (shield=sleeve to AGND at each jack) - COMPLETE 2026-07-31: bias parts, recovery networks, and op-amp power unit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
Routing and power headers
Send and recovery devices
Tank cable landings

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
